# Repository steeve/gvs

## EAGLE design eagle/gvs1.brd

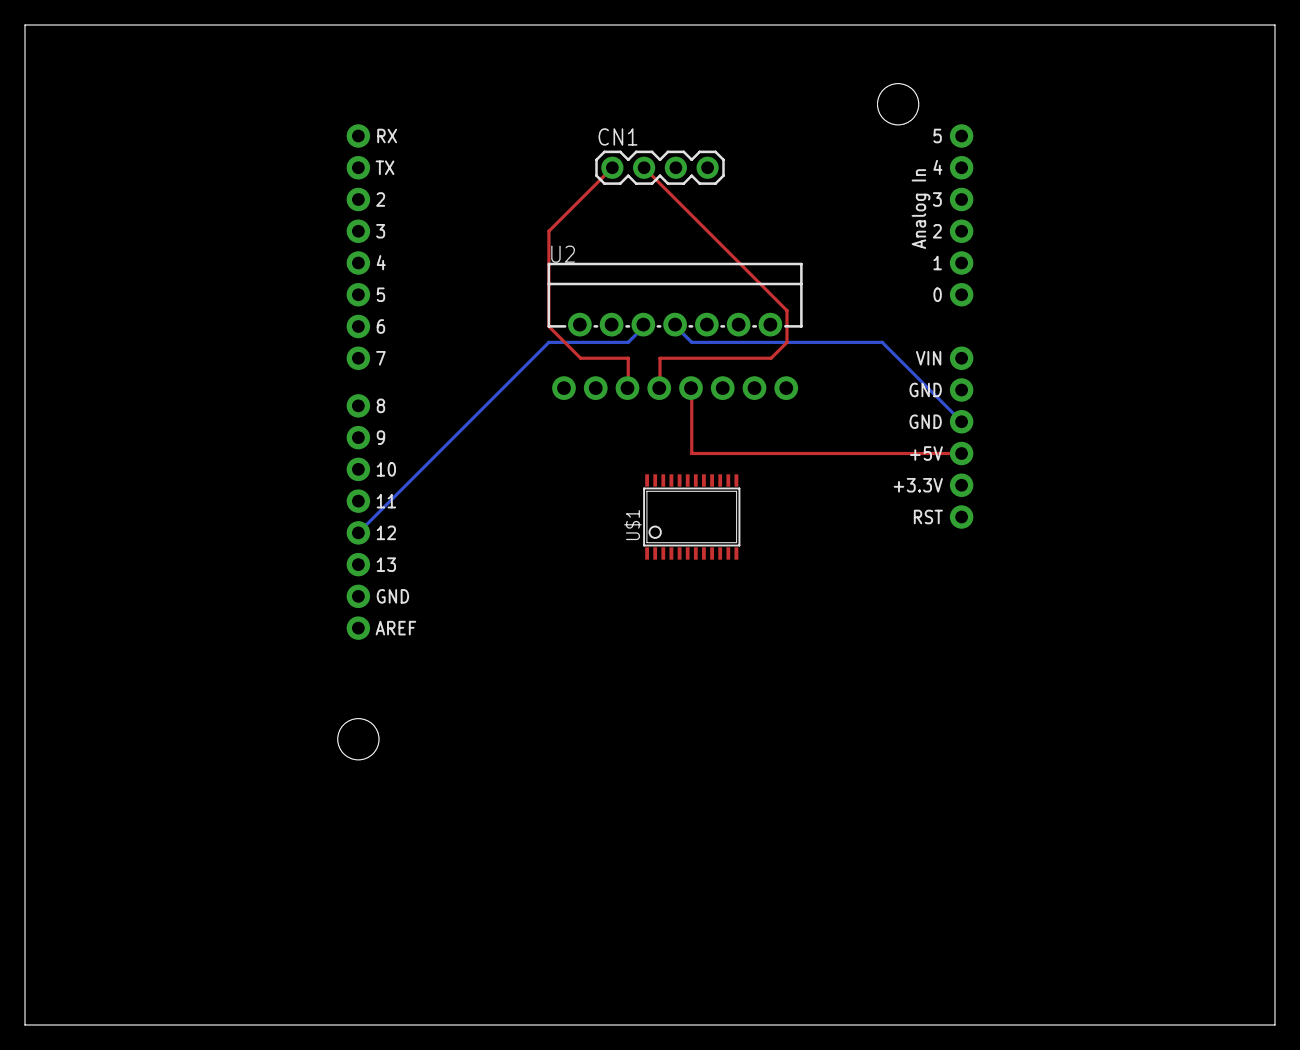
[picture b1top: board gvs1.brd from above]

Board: 2 copper layers, 100.0 x 80.0 mm, 4 parts (0 on the bottom side), 11 nets.

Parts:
CN1: 1X4-BIG; 1X04-BIG
U1: ARDUINO_SHIELDLABEL; DUEMILANOVE_SHIELD
U2: L298; MULTIWATT15
U$1: AD5410; TSSOP24

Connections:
+5V: U1.5V, U2.9
EAR1: CN1.1, U2.5
EAR2: CN1.2, U2.7
GND: U1.GND@0, U2.8, U$1.1
unnamed: U1.D11, U$1.9
unnamed: U1.D13, U$1.8
unnamed: U2.4, U$1.19
unnamed: U1.D12, U2.6
unnamed: U1.A0, U$1.20
unnamed: U1.D2, U$1.2, U$1.3
unnamed: U1.A1, U$1.18

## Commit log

2013-07-05 Remove useless files
2013-07-05 Directories
2013-07-05 Oops readme

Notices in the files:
parts and their libraries:
SparkFun-Boards: Licensing: CC v3.0 Share-Alike You are welcome to use this library for commercial purposes.
